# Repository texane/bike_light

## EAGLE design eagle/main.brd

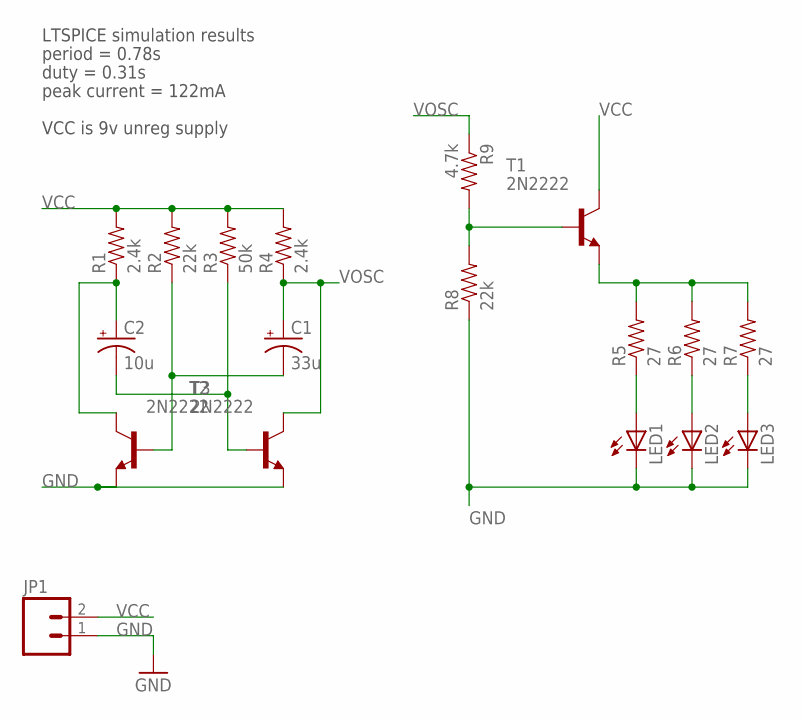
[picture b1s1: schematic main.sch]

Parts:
C1: 33u; CPOL-RADIAL-100UF-25V
C2: 10u; CPOL-RADIAL-100UF-25V
JP1: M02LOCK; 1X02_LOCK
LED1, LED2, LED3: LED5MM
R1, R4: 2.4k; AXIAL-0.4
R2, R8: 22k; AXIAL-0.4
R3: 50k; AXIAL-0.4
R5, R6, R7: 27; AXIAL-0.4
R9: 4.7k; AXIAL-0.4
T1, T2, T3: 2N2222; TO18

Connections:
GND: JP1.1, LED1.K (C), LED2.K (C), LED3.K (C), R8.P$1 (1), T2.1 (E), T3.1 (E)
unnamed: R5.P$2 (2), R6.P$2 (2), R7.P$2 (2), T1.1 (E)
unnamed: C1.2 (-), R2.P$1 (1), T2.2 (B)
unnamed: C2.2 (-), R3.P$1 (1), T3.2 (B)
unnamed: C2.1 (+), R1.P$1 (1), T2.3 (C)
unnamed: LED1.A, R5.P$1 (1)
unnamed: LED2.A, R6.P$1 (1)
unnamed: LED3.A, R7.P$1 (1)
unnamed: R8.P$2 (2), R9.P$2 (2), T1.2 (B)
VCC: JP1.2, R1.P$2 (2), R2.P$2 (2), R3.P$2 (2), R4.P$2 (2), T1.3 (C)
VOSC: C1.1 (+), R4.P$1 (1), R9.P$1 (1), T3.3 (C)

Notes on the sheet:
VCC is 9v unreg supply
LTSPICE simulation results
period = 0.78s
duty = 0.31s
peak current = 122mA

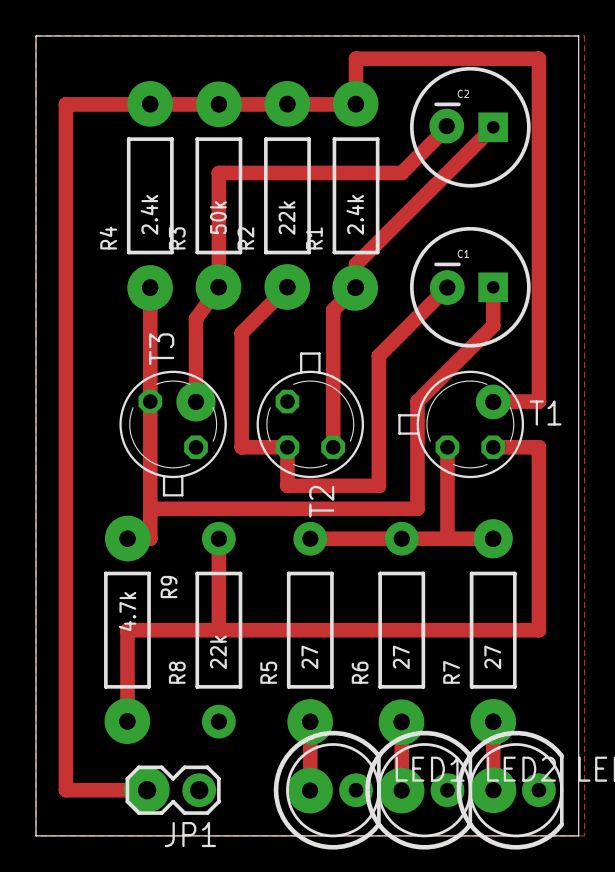
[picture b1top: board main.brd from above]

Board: 2 copper layers, 30.1 x 44.4 mm, 18 parts (0 on the bottom side), 11 nets.

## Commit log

2012-12-08 [ add ] ltspice/main_light.asc
2012-12-08 [ add ] eagle/main.sch
2012-12-09 [ update ] main.sch, simulation notes
2012-12-09 [ update ] main.sch, add connector
2012-12-09 [ add ] main.brd
2012-12-09 [ add ] add eagle/main.png
2012-12-09 [ add ] ../doc/notes
2012-12-09 [ update ] main.brd
2012-12-09 [ add ] pics
2012-12-09 [ add ] add vids

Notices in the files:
parts and their libraries:
SparkFun: Licensing: CC v3.0 Share-Alike You are welcome to use this library for commercial purposes.
